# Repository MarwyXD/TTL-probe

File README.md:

# TTL-probe

# This project is about creating cheap but also somehow functional probe for logic circuits.
# If you do a  lot things with procesors it will probably come in handy when you´ll have think like this with you.

# The eagle files i´m uploading is only a reference for you somehow (.brd), for sure you can use the .sch file and create your own PCB layout, or take mine, it´s up to you.

# This project is old like 3 years, i´m uploading it now becouse i said to myself that i could finaly upload something online too, and see how will (if someone) response.

# I wish you good luck with building it, all requerments you will find in the schematic or photos (like the parts etc.)

# Thank you.

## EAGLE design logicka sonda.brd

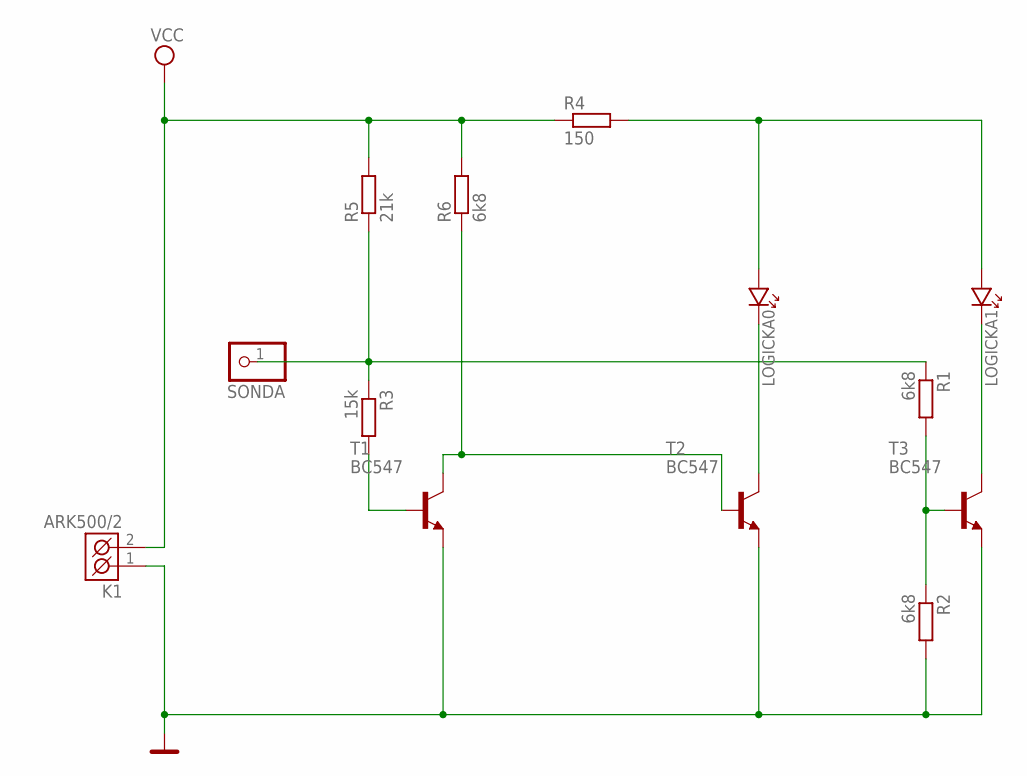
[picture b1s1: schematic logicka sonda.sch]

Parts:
K1: ARK500/2
LOGICKA0, LOGICKA1: LED_5
R1, R2, R6: 6k8; 0207/10
R3: 15k; 0207/10
R4: 150; 0207/10
R5: 21k; 0207/10
SONDA: PINHD-1X1; 1X01
T1, T2, T3: BC547; TO92

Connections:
GND: K1.1 (K1), R2.2, T1.1 (E), T2.1 (E), T3.1 (E)
LOGICKA1: LOGICKA1.K, T3.3 (C)
unnamed: R6.1, T1.3 (C), T2.2 (B)
unnamed: R3.2, T1.2 (B)
unnamed: R1.2, R2.1, T3.2 (B)
unnamed: LOGICKA0.K, T2.3 (C)
unnamed: LOGICKA0.A, LOGICKA1.A, R4.2
UF: R1.1, R3.1, R5.1, SONDA.1
VCC: K1.2 (K2), R4.1, R5.2, R6.2

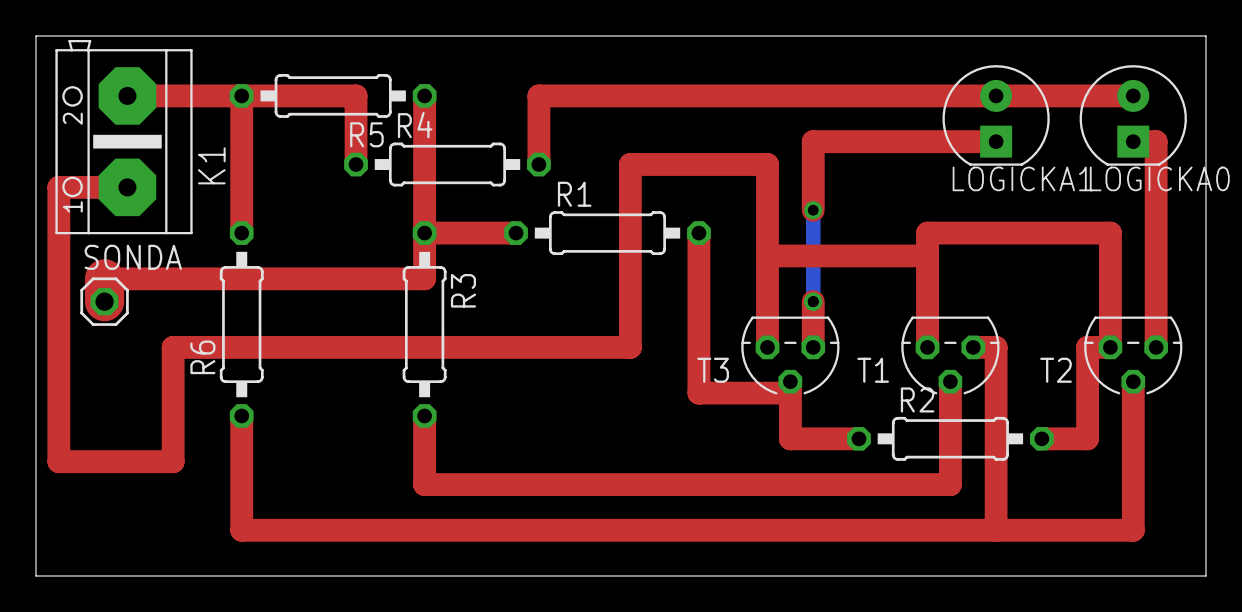
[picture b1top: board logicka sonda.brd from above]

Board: 2 copper layers, 65.0 x 30.0 mm, 13 parts (0 on the bottom side), 9 nets.

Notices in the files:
parts and their libraries:
Copyright (C) PaJa 2011-2014
Copyright (C) PaJa 2001-2014
